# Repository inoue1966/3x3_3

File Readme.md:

# 3x3 keyboard

 Use Arduino-Leonard.

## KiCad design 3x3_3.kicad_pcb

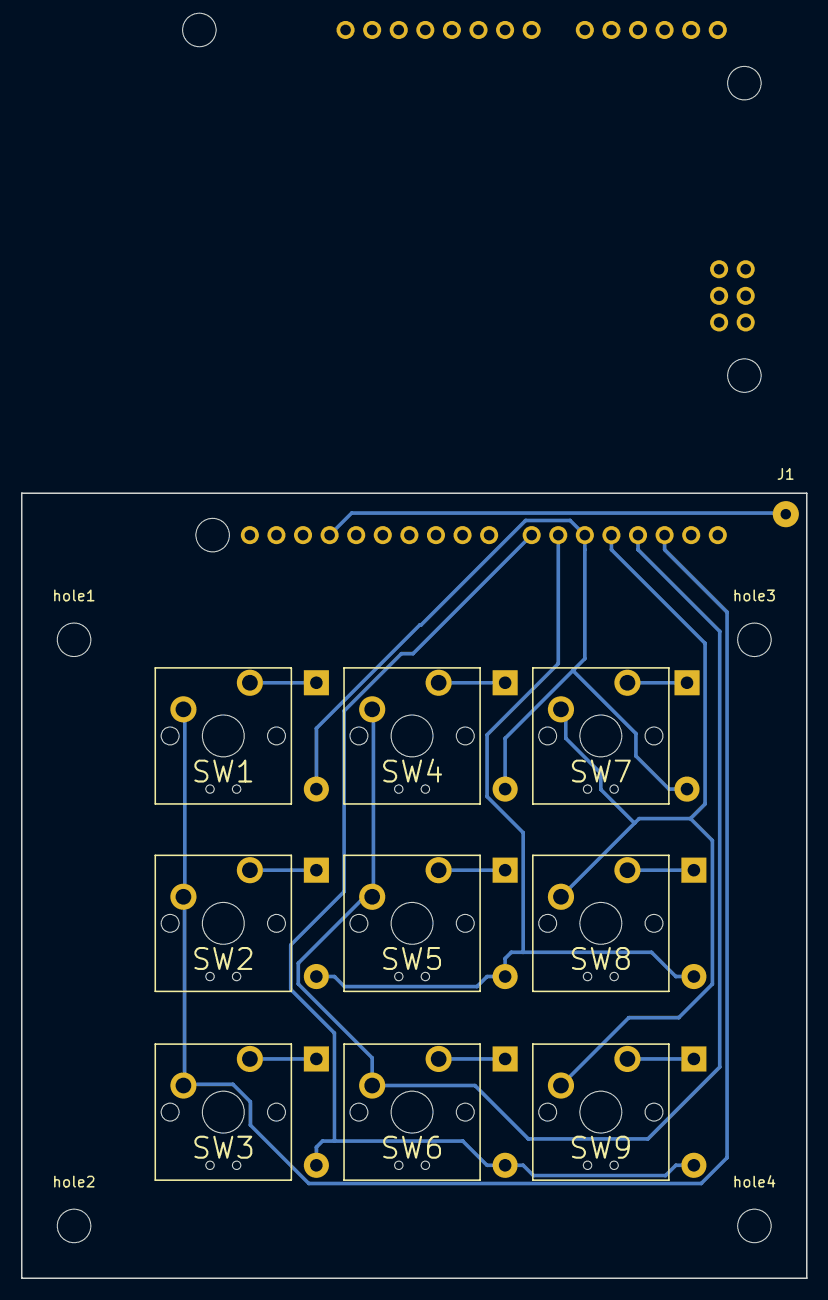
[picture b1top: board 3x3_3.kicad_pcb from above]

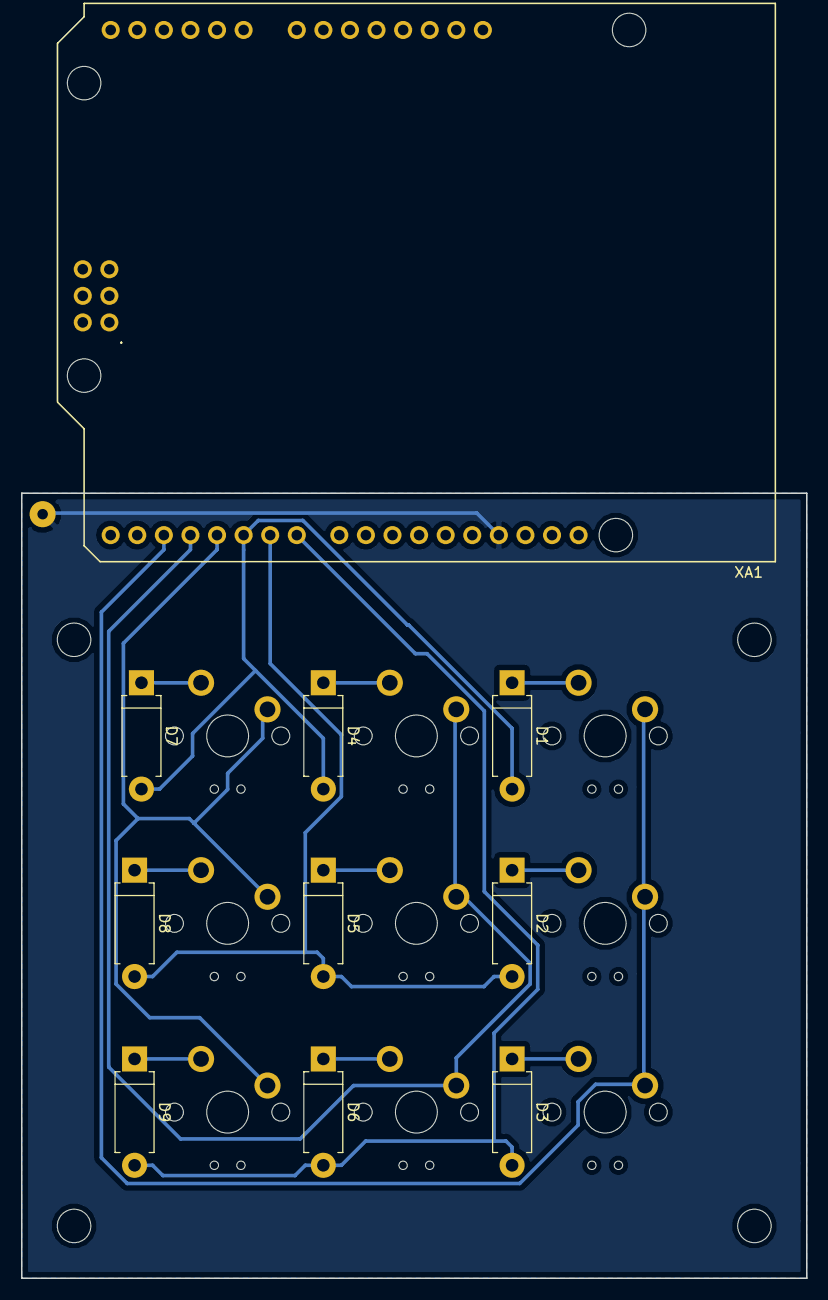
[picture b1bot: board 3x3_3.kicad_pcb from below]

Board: 2 copper layers, 75.0 x 75.0 mm, 24 parts (10 on the bottom side), 16 nets.

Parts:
D1, D2, D3, D4, D5, D6, D7, D8, D9: DIODE; D_DO-15_P10.16mm_Horizontal
J1: Conn_01x01_Male; SolderWirePad_single_1mmDrill
SW1, SW2, SW3, SW4, SW5, SW6, SW7, SW8, SW9: SW_Push; switch
XA1: Arduino_Leonardo_Shield
hole1, hole2, hole3, hole4: MountingHole_3.2mm_M3

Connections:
/col0: SW1.1, SW2.1, SW3.1, XA1.D2
/col1: SW4.1, SW5.1, SW6.1, XA1.D3
/col2: SW7.1, SW8.1, SW9.1, XA1.D4
/row0: D1.2, D4.2, D7.2, XA1.D5
/row1: D2.2, D5.2, D8.2, XA1.D6
/row2: D3.2, D6.2, D9.2, XA1.D7
GND: J1.1, XA1.GND1
unnamed: D1.1, SW1.2
unnamed: D2.1, SW2.2
unnamed: D3.1, SW3.2
unnamed: D4.1, SW4.2
unnamed: D5.1, SW5.2
unnamed: D6.1, SW6.2
unnamed: D7.1, SW7.2
unnamed: D8.1, SW8.2
unnamed: D9.1, SW9.2

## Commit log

2018-09-17 first
2018-09-17 .gitignore
2018-09-17 Readme.md
2018-09-17 クリアランスと太さを0.3に
